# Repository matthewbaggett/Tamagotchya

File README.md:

Tamagotchya
===========

A 2019 Tamagotchi clone using:
 * ESP 32 dual-core embedded wifi/bluetooth microcontroller
 * 4/8/16MB SPI flash on board
 * UT-0206-P05 monochrome oLED display
 * [ADXL345](References/ADXL345.pdf) Accellerometer
 * [USB C socket](References/XKB-U262-16XN-4BVC11_C319148.pdf) for charging and USB2.0 data
 * [CP2102N](References/SILICON-LABS-CP2102N-A01-GQFN20_C89049.pdf) Silicon Labs USB UART for interaction with a PCB 
 (and firmware loading)
 * [5 direction joypad](References/SF303GJ26-3.pdf) Up/Down/Left/Right/Click 
 * [TP4056](References/TP4056.pdf) 1A lithium battery charger for 300mAh-ish li-poly cell
 * [FS312](References/FS312.pdf) Battery over/under discharge protection, battery level monitoring using voltage divider and ESP's analog input.
 
## Render

Render is of rear of device. Clearance at top of board is for solder-down connector of this oLED LCD, bent over and folded over the PCB:

## PCB

## Schematics

## License
This project is licensed under the The TAPR Open Hardware License.

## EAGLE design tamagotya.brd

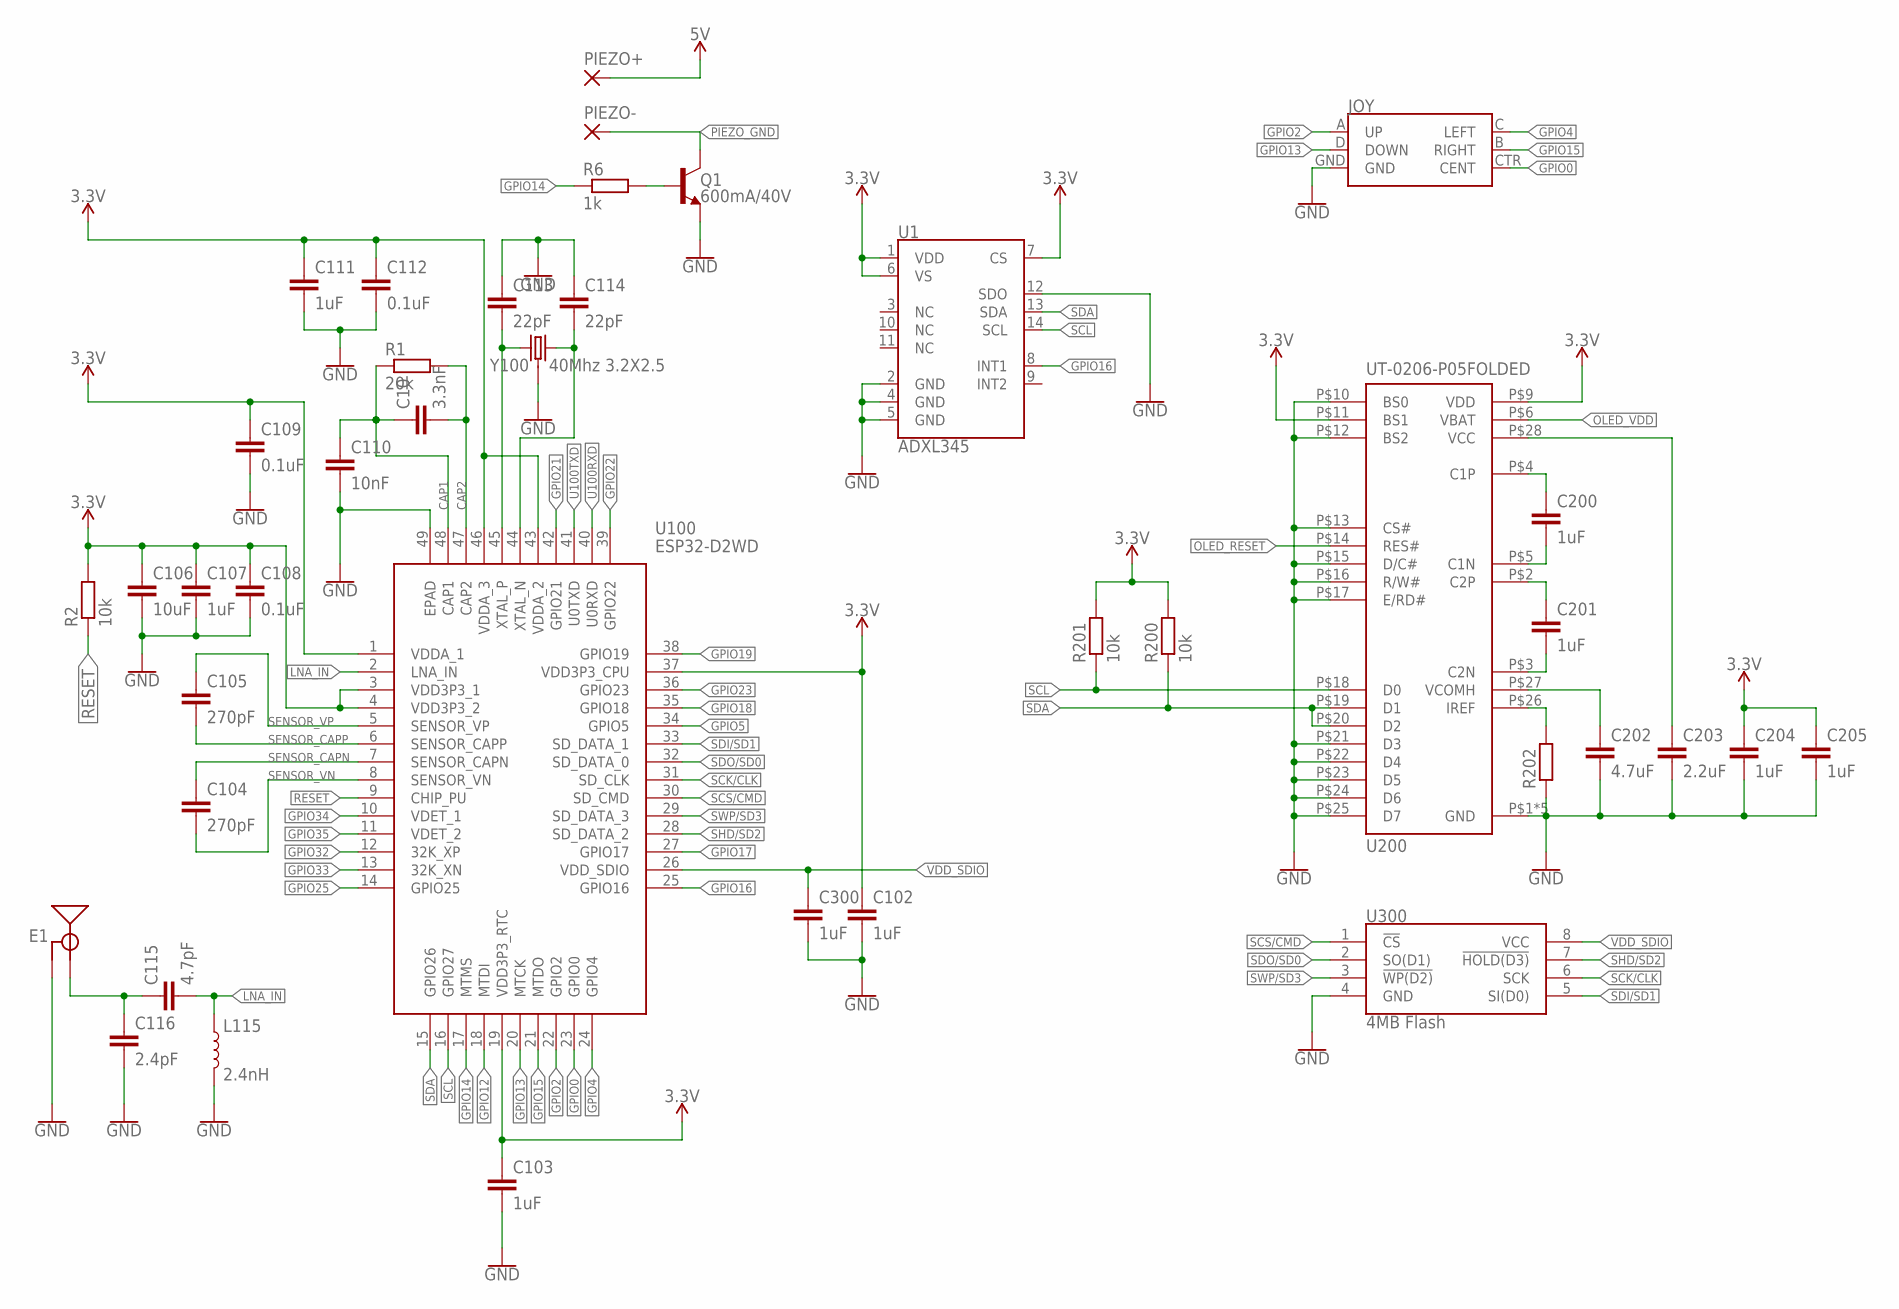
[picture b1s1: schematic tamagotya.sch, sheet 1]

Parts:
C10: 3.3nF; C0603
C102, C103, C107, C111, C200, C201, C204, C205, C300: 1uF; C0603
C104, C105: 270pF; C0603
C106: 10uF; C0603
C108, C109, C112: 0.1uF; C0603
C110: 10nF; C0603
C113, C114: 22pF; C0603
C115: 4.7pF; C0603
C116: 2.4pF; C0603
C202: 4.7uF; C0603
C203: 2.2uF; C0603
E1: ANTENNA-GROUNDEDTRACE-15.2MM; TRACE_ANTENNA_2.4GHZ_15.2MM
JOY: JOYSTICK_MINI
L115: 2.4nH; 0603
PIEZO+: WIREPADSMD1,27-254; SMD1,27-2,54
PIEZO-: WIREPADSMD1,27-254; SMD1,27-2,54
Q1: 600mA/40V; SOT23-3
R1: 20k; R0603
R2, R200, R201: 10k; R0603
R6: 1k; R0603
R202: R-EU_R0603; R0603
U1: ADXL345; LGA-14
U100: ESP32-D2WD; QFN35P500X500X90-49N
U200: UT-0206-P05FOLDED; UT-0206-P05-FOLD
U300: 4MB Flash; SO08
Y100: 40Mhz 3.2X2.5; CRYSTAL-SMD-3.2X2.5MM

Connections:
3.3V: C102.1, C103.1, C106.1, C107.1, C108.1, C109.1, C111.1, C112.1, C204.1, C205.1, R2.2, R200.2, R201.2, U1.1 (VDD), U1.6 (VS), U1.7 (CS), U100.1 (VDDA_1), U100.3 (VDD3P3_1), U100.4 (VDD3P3_2), U100.19 (VDD3P3_RTC), U100.37 (VDD3P3_CPU), U100.43 (VDDA_2), U100.46 (VDDA_3), U200.P$9 (VDD), U200.P$11 (BS1); also elsewhere on the board
5V: PIEZO+.1; also elsewhere on the board
CAP1: C10.1, C110.1, R1.1, U100.48 (CAP1)
CAP2: C10.2, R1.2, U100.47 (CAP2)
GND: C102.2, C103.2, C106.2, C107.2, C108.2, C109.2, C110.2, C111.2, C112.2, C113.1, C114.1, C116.2, C202.2, C203.2, C204.2, C205.2, C300.2, E1.GND, JOY.GND, L115.2, Q1.2 (E), R202.1, U1.2 (GND), U1.4 (GND), U1.5 (GND), U1.12 (SDO), U100.49 (EPAD), U200.P$1 (GND), U200.P$7 (GND), U200.P$8 (GND), U200.P$10 (BS0), U200.P$12 (BS2), U200.P$13 (CS#), U200.P$15 (D/C#), U200.P$16 (R/W#), U200.P$17 (E/RD#), U200.P$21 (D3), U200.P$22 (D4), U200.P$23 (D5), U200.P$24 (D6), U200.P$25 (D7), U200.P$29 (GND), U200.P$30 (GND), U300.4 (GND), Y100.2 (3), Y100.4 (3); also elsewhere on the board
GPIO0: JOY.CTR (CENT), U100.23 (GPIO0); also elsewhere on the board
GPIO2: JOY.A (UP), U100.22 (GPIO2)
GPIO4: JOY.C (LEFT), U100.24 (GPIO4)
GPIO5: U100.34 (GPIO5)
GPIO12: U100.18 (MTDI)
GPIO13: JOY.D (DOWN), U100.20 (MTCK)
GPIO14: R6.1, U100.17 (MTMS)
GPIO15: JOY.B (RIGHT), U100.21 (MTDO)
GPIO16: U1.8 (INT1), U100.25 (GPIO16)
GPIO17: U100.27 (GPIO17)
GPIO18: U100.35 (GPIO18)
GPIO19: U100.38 (GPIO19)
GPIO21: U100.42 (GPIO21)
GPIO22: U100.39 (GPIO22)
GPIO23: U100.36 (GPIO23)
GPIO25: U100.14 (GPIO25)
GPIO32: U100.12 (32K_XP)
GPIO33: U100.13 (32K_XN)
GPIO34: U100.10 (VDET_1)
GPIO35: U100.11 (VDET_2)
LNA_IN: C115.2, L115.1, U100.2 (LNA_IN)
unnamed: Q1.1 (B), R6.2
unnamed: C115.1, C116.1, E1.ANT (SIGNAL)
unnamed: R202.2, U200.P$26 (IREF)
unnamed: C202.1, U200.P$27 (VCOMH)
unnamed: C200.1, U200.P$4 (C1P)
unnamed: C200.2, U200.P$5 (C1N)
unnamed: C201.1, U200.P$2 (C2P)
unnamed: C201.2, U200.P$3 (C2N)
unnamed: C203.1, U200.P$28 (VCC)
OLED_RESET: U200.P$14 (RES#)
OLED_VDD: U200.P$6 (VBAT)
PIEZO_GND: PIEZO-.1, Q1.3 (C)
RESET: R2.1, U100.9 (CHIP_PU); also elsewhere on the board
SCK/CLK: U100.31 (SD_CLK), U300.6 (SCK)
SCL: R201.1, U1.14 (SCL), U100.16 (GPIO27), U200.P$18 (D0)
SCS/CMD: U100.30 (SD_CMD), U300.1 (!CS)
SDA: R200.1, U1.13 (SDA), U100.15 (GPIO26), U200.P$19 (D1), U200.P$20 (D2)
SDI/SD1: U100.33 (SD_DATA_1), U300.5 (SI(D0))
SDO/SD0: U100.32 (SD_DATA_0), U300.2 (SO(D1))
SENSOR_CAPN: C104.1, U100.7 (SENSOR_CAPN)
SENSOR_CAPP: C105.2, U100.6 (SENSOR_CAPP)
SENSOR_VN: C104.2, U100.8 (SENSOR_VN)
SENSOR_VP: C105.1, U100.5 (SENSOR_VP); also elsewhere on the board
SHD/SD2: U100.28 (SD_DATA_2), U300.7 (!HOLD(D3))
SWP/SD3: U100.29 (SD_DATA_3), U300.3 (!WP(D2))
U100RXD: U100.40 (U0RXD); also elsewhere on the board
U100TXD: U100.41 (U0TXD); also elsewhere on the board
VDD_SDIO: C300.1, U100.26 (VDD_SDIO), U300.8 (VCC)
XTAL_P: C113.2, U100.45 (XTAL_P), Y100.1
XTAN_N: C114.2, U100.44 (XTAL_N), Y100.3 (2)

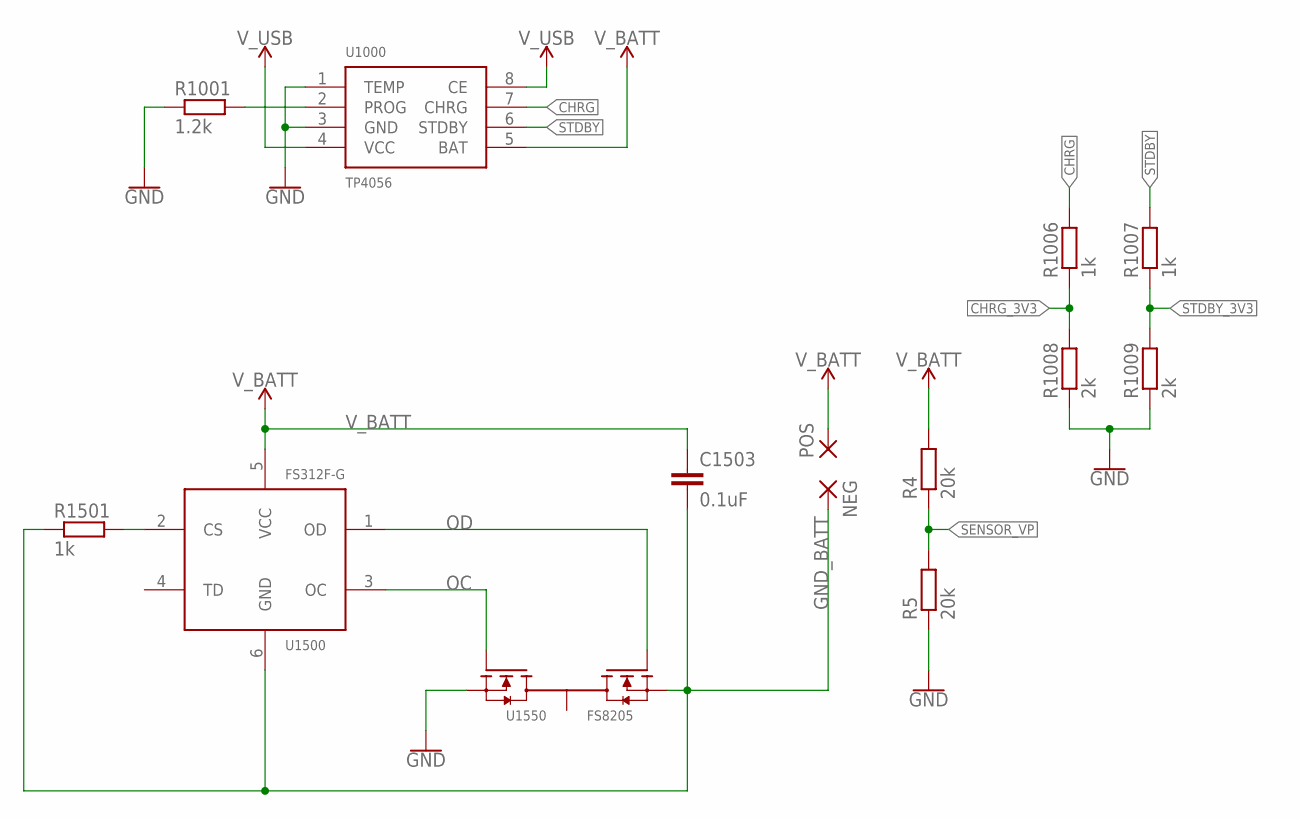
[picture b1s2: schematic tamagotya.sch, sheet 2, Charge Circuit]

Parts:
C1503: 0.1uF; C0603
NEG: SMD5; SMD2,54-5,08
POS: SMD5; SMD2,54-5,08
R4, R5: 20k; R0603
R1001: 1.2k; R0603
R1006, R1007, R1501: 1k; R0603
R1008, R1009: 2k; R0603
U1000: TP4056; SOP-8
U1500: FS312F-G; SOT23-6
U1550: FS8205; SOT23-6

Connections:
CHRG: R1006.2, U1000.7 (CHRG)
CHRG_3V3: R1006.1, R1008.2
FS_CS: R1501.2, U1500.2 (CS)
GND: R5.1, R1001.1, R1008.1, R1009.1, U1000.1 (TEMP), U1000.3 (GND), U1550.1 (S1); also elsewhere on the board
GND_BATT: C1503.2, NEG.1, R1501.1, U1500.6 (GND), U1550.3 (S2)
unnamed: R1001.2, U1000.2 (PROG)
OC: U1500.3 (OC), U1550.6 (G1)
OD: U1500.1 (OD), U1550.4 (G2)
SENSOR_VP: R4.1, R5.2; also elsewhere on the board
STDBY: R1007.2, U1000.6 (STDBY)
STDBY_3V3: R1007.1, R1009.2
V_BATT: C1503.1, POS.1, R4.2, U1000.5 (BAT), U1500.5 (VCC); also elsewhere on the board
V_USB: U1000.4 (VCC), U1000.8 (CE); also elsewhere on the board

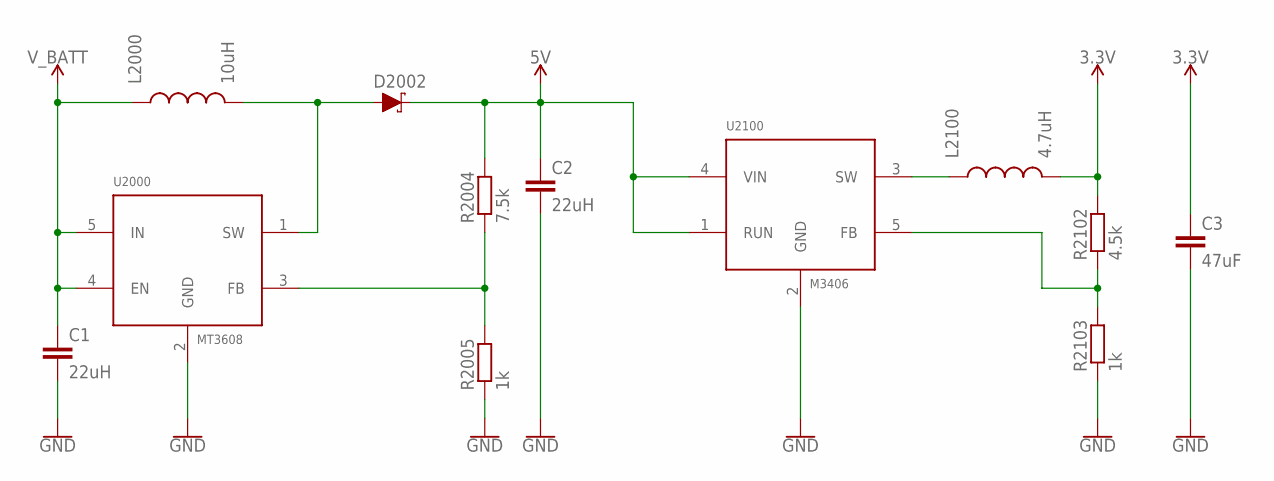
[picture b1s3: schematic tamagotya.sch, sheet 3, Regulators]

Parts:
C1, C2: 22uH; C0603
C3: 47uF; C0805
D2002: DIODE-SCHOTTKY-PMEG4005EJ; SOD-323
L2000: 10uH; INDUCTOR_3.0X3.0
L2100: 4.7uH; INDUCTOR_3.0X3.0
R2004: 7.5k; R0603
R2005, R2103: 1k; R0603
R2102: 4.5k; R0603
U2000: MT3608; SOT23-6
U2100: M3406; SOT23-5

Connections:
3.3V: C3.1, L2100.P$2 (2), R2102.2; also elsewhere on the board
5V: C2.1, D2002.C, R2004.2, U2100.1 (RUN), U2100.4 (VIN); also elsewhere on the board
BUCK: D2002.A, L2000.P$2 (2), U2000.1 (SW)
GND: C1.2, C2.2, C3.2, R2005.1, R2103.1, U2000.2 (GND), U2100.2 (GND); also elsewhere on the board
unnamed: R2004.1, R2005.2, U2000.3 (FB)
unnamed: L2100.P$1 (1), U2100.3 (SW)
unnamed: R2102.1, R2103.2, U2100.5 (FB)
V_BATT: C1.1, L2000.P$1 (1), U2000.4 (EN), U2000.5 (IN); also elsewhere on the board

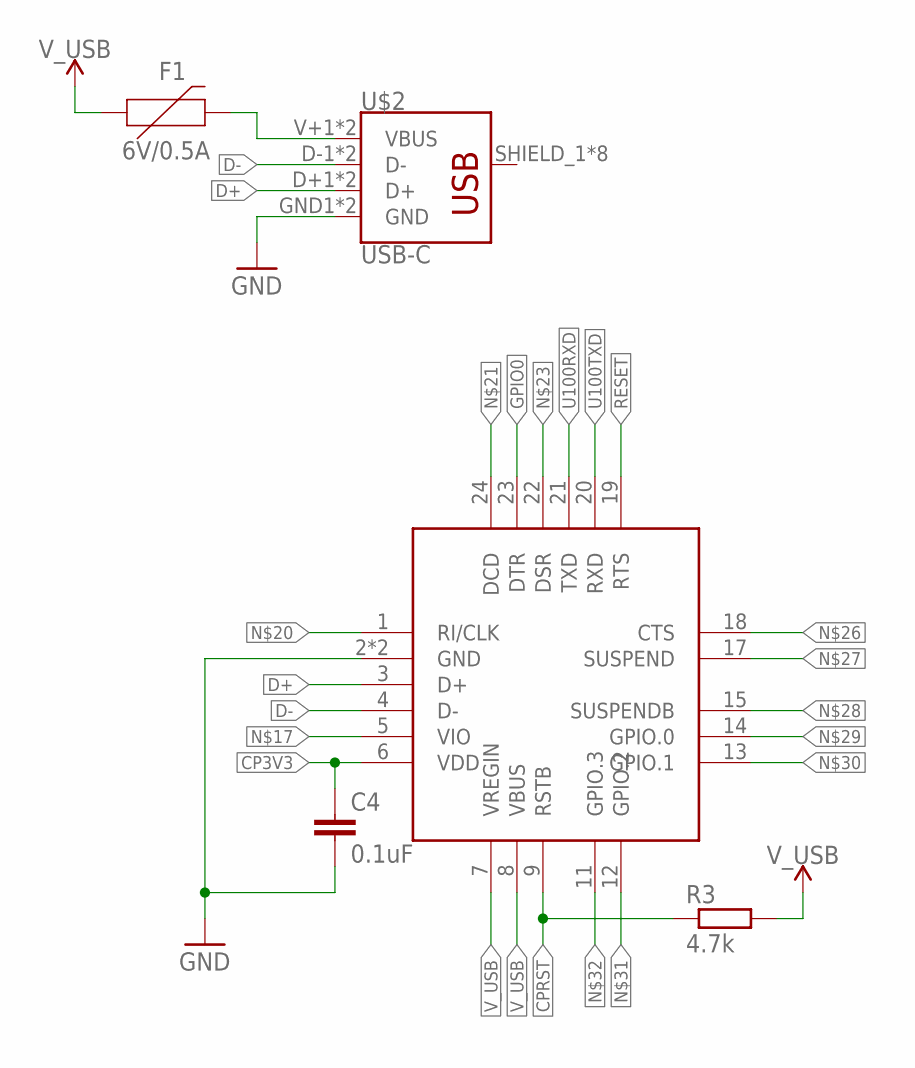
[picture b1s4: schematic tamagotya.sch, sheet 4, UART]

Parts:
C4: 0.1uF; C0603
F1: 6V/0.5A; 1206
R3: 4.7k; R0603
U$2: USB-C; USB_C-XKBENTERPRISEU262-16XN-4BVC11
U$3: CP2102N-QFN24; QFN24-4X4

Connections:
CP3V3: C4.1, U$3.6 (VDD)
CPRST: R3.1, U$3.9 (RSTB)
D+: U$2.D+1 (D+), U$2.D+2 (D+), U$3.3 (D+)
D-: U$2.D-1 (D-), U$2.D-2 (D-), U$3.4 (D-)
GND: C4.2, U$2.GND1 (GND), U$2.GND2 (GND), U$3.2 (GND), U$3.EXP (GND); also elsewhere on the board
GPIO0: U$3.23 (DTR); also elsewhere on the board
RESET: U$3.19 (RTS); also elsewhere on the board
U100RXD: U$3.21 (TXD); also elsewhere on the board
U100TXD: U$3.20 (RXD); also elsewhere on the board
V_USB: F1.1, R3.2, U$3.7 (VREGIN), U$3.8 (VBUS); also elsewhere on the board
V_USB_UNFUSED: F1.2, U$2.V+1 (VBUS), U$2.V+2 (VBUS)

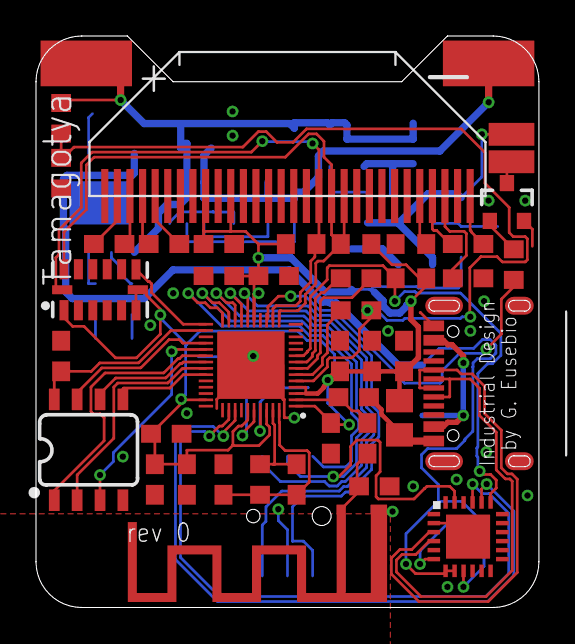
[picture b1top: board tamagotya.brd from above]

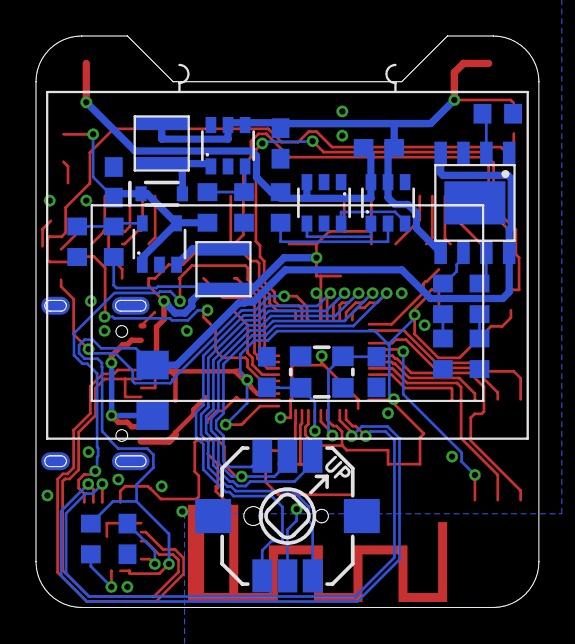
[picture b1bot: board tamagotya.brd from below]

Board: 2 copper layers, 27.9 x 31.8 mm, 71 parts (29 on the bottom side), 61 nets.

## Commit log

2019-01-24 Laid out, need to add charge/boost circuit and its basically done. Could do with a UART too.
2019-01-24 Almost there. Mostly laid out. Just got CP2102 power to resolve.
2019-01-25 CP2102 now has adequate power circuitry, I believe
2019-01-25 Accellerometer ADXL345 with i2c + 1 interrupt.
2019-01-25 Adding ADXL345 datasheet
2019-01-25 Done: ADC sensing battery voltage.
2019-01-25 Add a NPN transitor to drive a piezo speaker
2019-01-25 Rejig to remove extra labels
2019-01-25 Fix collision between antenna and switch holes
2019-01-25 Futzing about with the edges of the ground plane layout
2019-08-01 Tamagotcha documentation
2019-08-01 Crop down images
2019-08-02 Rejig for github pages
2019-08-02 Set theme jekyll-theme-hacker

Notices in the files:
parts and their libraries:
SparkFun-RF: Licensing: Creative Commons ShareAlike 4.0 International - https://creativecommons.org/licenses/by-sa/4.0
